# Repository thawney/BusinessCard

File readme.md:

# Thawney's Ultimate Business Card Of Businessynes

Ello! Thawney here :D this is my business card. It is a very simple design based on the atari punk console that gives the user a pitch and modulation knob and control voltage input and can be powered from a 9v battery.

It is recommended to use alpha 9mm potentiometer but any will do! The audio/cv in jacks are thonkicon (WQP518MA). If you are Bristol based then come and visit Bristol Communal Modular on a Tuesday, they might have some spares.

!!NOTE!! If you are one of the lovely people who came to my Dorkbot Bristol talk on 11/06/2024 then the business cards I gave you have the potentiometers wired backwards for pitch and modulation, I'm sorry D:

# Hacking the Card

There are a lot of fun hacks you can do! For example, the potentiometers are wired as variable resistors which means you can replace them with fun resistors (Like LDRs or Thermistors) and control the card in new fun ways.

To do this just ensure that you are placing the legs of your components in pins that ARE NOT already connected with the components!

If you want to do something less technical, try heating up or cooling the chip on the circuit board to mess with the tuning!

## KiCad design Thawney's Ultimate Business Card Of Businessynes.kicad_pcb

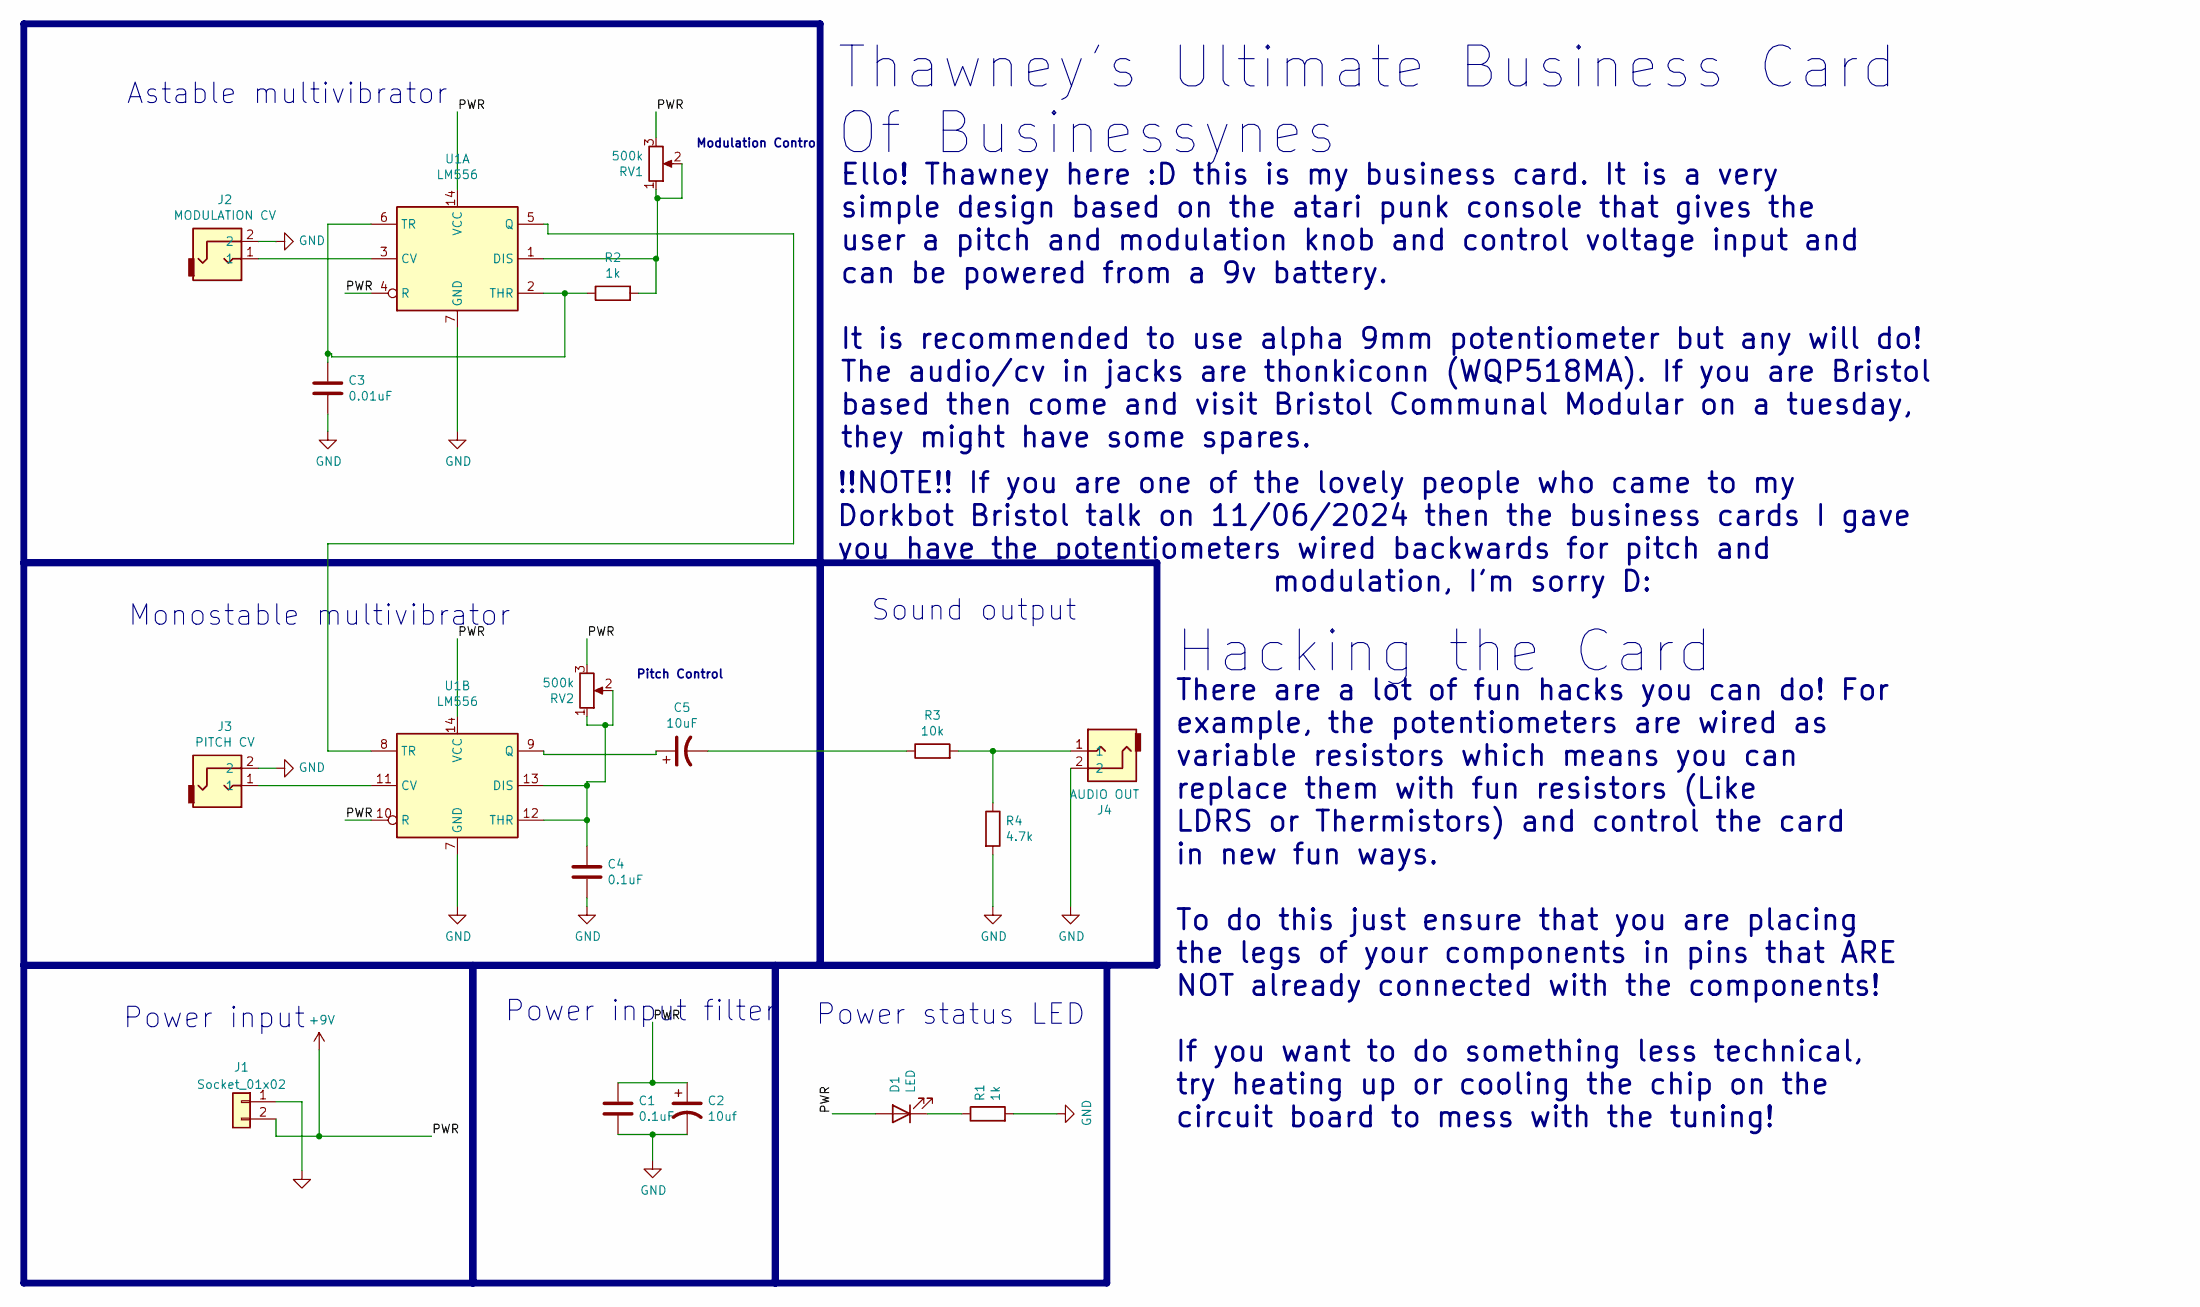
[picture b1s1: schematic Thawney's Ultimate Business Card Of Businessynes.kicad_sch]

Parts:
C1, C4: 0.1uF; C_0603_1608Metric
C2: 10uf; C_0603_1608Metric
C3: 0.01uF; C_0603_1608Metric
C5: 10uF; C_0603_1608Metric
D1: LED; LED_0603_1608Metric
J1: Socket_01x02; PinSocket_1x02_P2.54mm_Vertical; Part Number ?
J2: MODULATION CV; EighthInch_PJ398SM
J3: PITCH CV; EighthInch_PJ398SM
J4: AUDIO OUT; EighthInch_PJ398SM
R1, R2: 1k; R_0603_1608Metric
R3: 10k; R_0603_1608Metric
R4: 4.7k; R_0603_1608Metric
RV1, RV2: 500k; Pot_9mm_DShaft
U1: LM556; SOIC-14_3.9x8.7mm_P1.27mm

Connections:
+9V: C1.1, C2.1, D1.2 (A), J1.2, RV1.3, RV2.3, U1.4 (R), U1.10 (R), U1.14 (VCC)
GND: C1.2, C2.2, C3.2, C4.2, J1.1, J2.2, J3.2, J4.2, R1.2, R4.2, U1.7 (GND)
unnamed: C5.2, R3.1
unnamed: D1.1 (K), R1.1
unnamed: J4.1, R3.2, R4.1
unnamed: J2.1, U1.3 (CV)
unnamed: R2.2, RV1.1, RV1.2, U1.1 (DIS)
unnamed: U1.5 (Q), U1.8 (TR)
unnamed: C3.1, R2.1, U1.2 (THR), U1.6 (TR)
unnamed: J3.1, U1.11 (CV)
unnamed: C4.1, RV2.1, RV2.2, U1.12 (THR), U1.13 (DIS)
unnamed: C5.1, U1.9 (Q)

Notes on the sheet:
Thawney's Ultimate Business Card Of Businessynes
Ello! Thawney here :D this is my business card. It is a very simple design based on the atari punk console that gives the user a pitch and modulation knob and control voltage input and can be powered from a 9v battery. It is recommended to use alpha 9mm potentiometer but any will do! The audio/cv i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
There are a lot of fun hacks you can do! For example, the potentiometers are wired as variable resistors which means you can replace them with fun resistors (Like LDRS or Thermistors) and control the card in new fun ways. To do this just ensure that you are placing the legs of your components in pi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
Sound output
Power status LED
Power input
Hacking the Card
Monostable multivibrator
!!NOTE!! If you are one of the lovely people who came to my Dorkbot Bristol talk on 11/06/2024 then the business cards I gave you have the potentiometers wired backwards for pitch and modulation, I'm sorry D:
Pitch Control
Astable multivibrator
Power input filter
Modulation Control

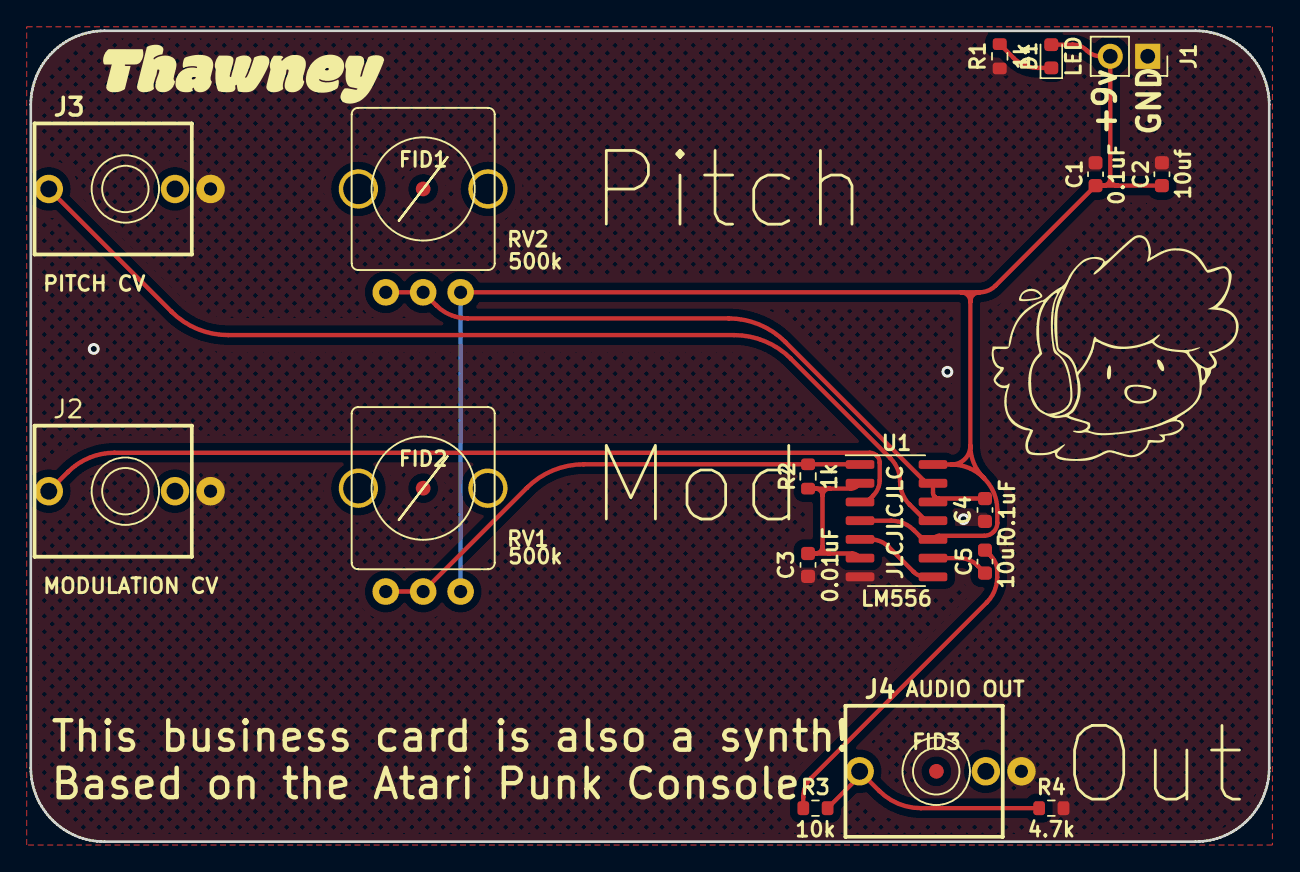
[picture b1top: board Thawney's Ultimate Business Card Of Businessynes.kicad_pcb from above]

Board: 2 copper layers, 84.0 x 55.0 mm, 20 parts (0 on the bottom side), 12 nets.

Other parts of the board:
FID1, FID2, FID3: Fiducial_1mm_Mask2mm

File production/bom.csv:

Designator,Footprint,Quantity,Value,LCSC Part #
"C1, C4",0603,2,0.1uF,
"C2, C5",0603,2,10uf,
C3,0603,1,0.01uF,
D1,0603,1,LED,
"FID1, FID2, FID3",Fiducial_1mm_Mask2mm,3,Fiducial_1mm_Mask2mm,
J1,PinSocket_1x02_P2.54mm_Vertical,1,Socket_01x02,
J2,EighthInch_PJ398SM,1,MODULATION CV,
J3,EighthInch_PJ398SM,1,PITCH CV,
J4,EighthInch_PJ398SM,1,AUDIO OUT,
"R1, R2",0603,2,1k,
R3,0603,1,10k,
R4,0603,1,4.7k,
"RV1, RV2",Pot_9mm_DShaft,2,500k,
U1,SOIC-14_3.9x8.7mm_P1.27mm,1,LM556,

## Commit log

2024-06-12 First Commit!
    Hello World :D
